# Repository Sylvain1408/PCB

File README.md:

# PCB
Those PCB are done with Cadence and Eagle.

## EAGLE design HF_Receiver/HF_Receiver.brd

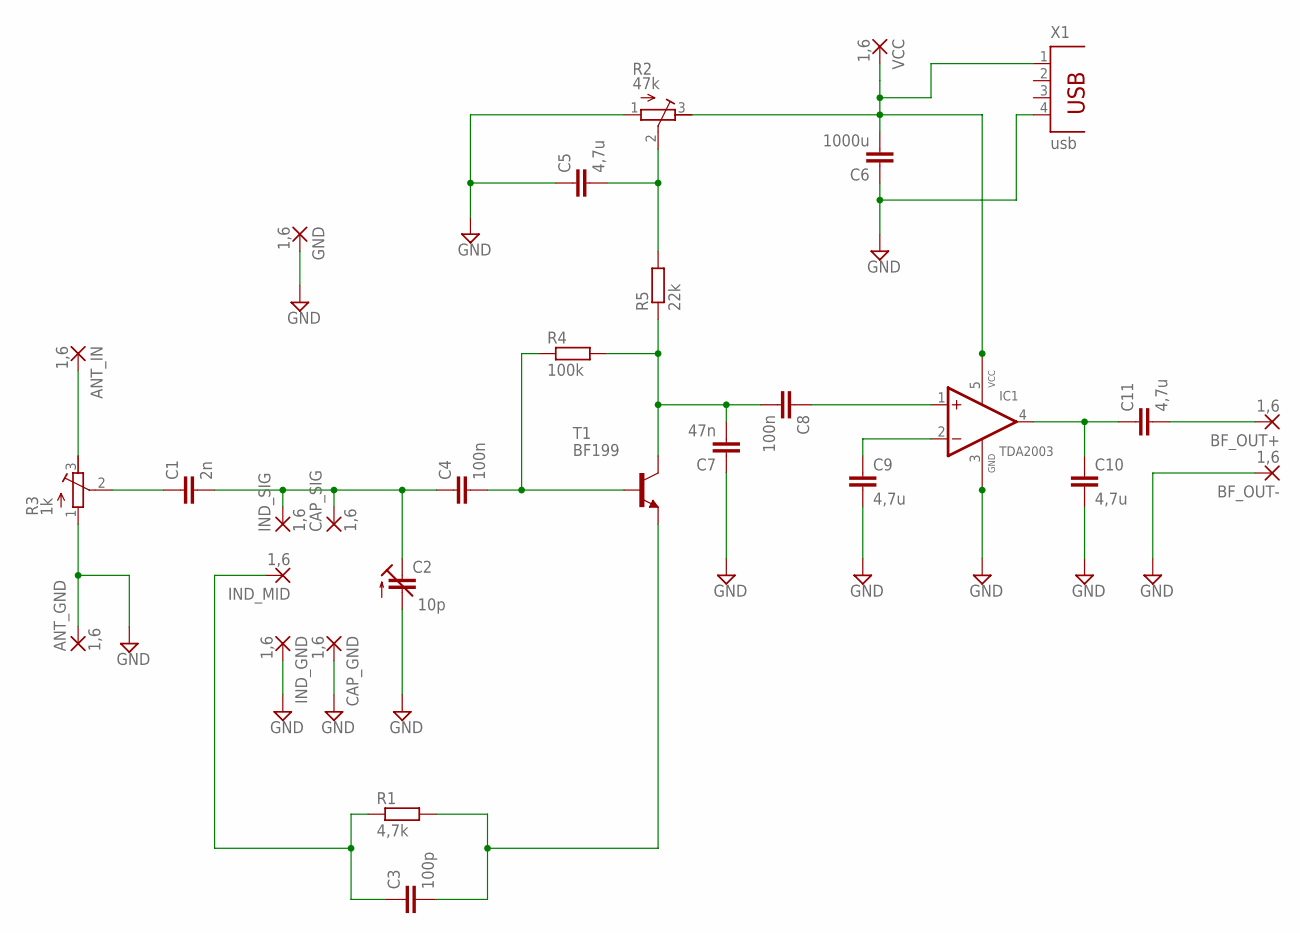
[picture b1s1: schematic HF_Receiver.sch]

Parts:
ANT_GND: 1,6; 1,6/0,9
ANT_IN: 1,6; 1,6/0,9
BF_OUT+: 1,6; 1,6/0,9
BF_OUT-: 1,6; 1,6/0,9
C1: 2n; C075-032X103
C2: 10p; CTRIM808-BC
C3: 100p; C075-032X103
C4, C8: 100n; C075-032X103
C5, C9, C10, C11: 4,7u; C075-032X103
C6: 1000u; C075-032X103
C7: 47n; C075-032X103
CAP_GND: 1,6; 1,6/0,9
CAP_SIG: 1,6; 1,6/0,9
GND: 1,6; 1,6/0,9
IC1: TDA2003; PENTAWATT-V
IND_GND: 1,6; 1,6/0,9
IND_MID: 1,6; 1,6/0,9
IND_SIG: 1,6; 1,6/0,9
R1: 4,7k; 0207/10
R2: 47k; RTRIM3339P
R3: 1k; RTRIM3339P
R4: 100k; 0207/10
R5: 22k; 0207/10
T1: BF199; TO92
VCC: 1,6; 1,6/0,9
X1: usb; PN87520

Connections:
GND: ANT_GND.1, BF_OUT-.1, C2.2 (A), C5.1, C6.1, C7.1, C9.2, C10.2, CAP_GND.1, GND.1, IC1.3 (GND), IND_GND.1, R2.1 (A), R3.1 (A), X1.4
unnamed: ANT_IN.1, R3.3 (E)
unnamed: C1.1, R3.2 (S)
unnamed: C1.2, C2.1 (E), C4.1, CAP_SIG.1, IND_SIG.1
unnamed: C3.1, IND_MID.1, R1.1
unnamed: C3.2, R1.2, T1.2 (E)
unnamed: C4.2, R4.1, T1.1 (B)
unnamed: C8.1, IC1.1 (+IN)
unnamed: C7.2, C8.2, R4.2, R5.1, T1.3 (C)
unnamed: C5.2, R2.2 (S), R5.2
unnamed: C9.1, IC1.2 (-IN)
unnamed: C10.1, C11.1, IC1.4 (OUT)
unnamed: BF_OUT+.1, C11.2
VCC: C6.2, IC1.5 (VCC), R2.3 (E), VCC.1, X1.1

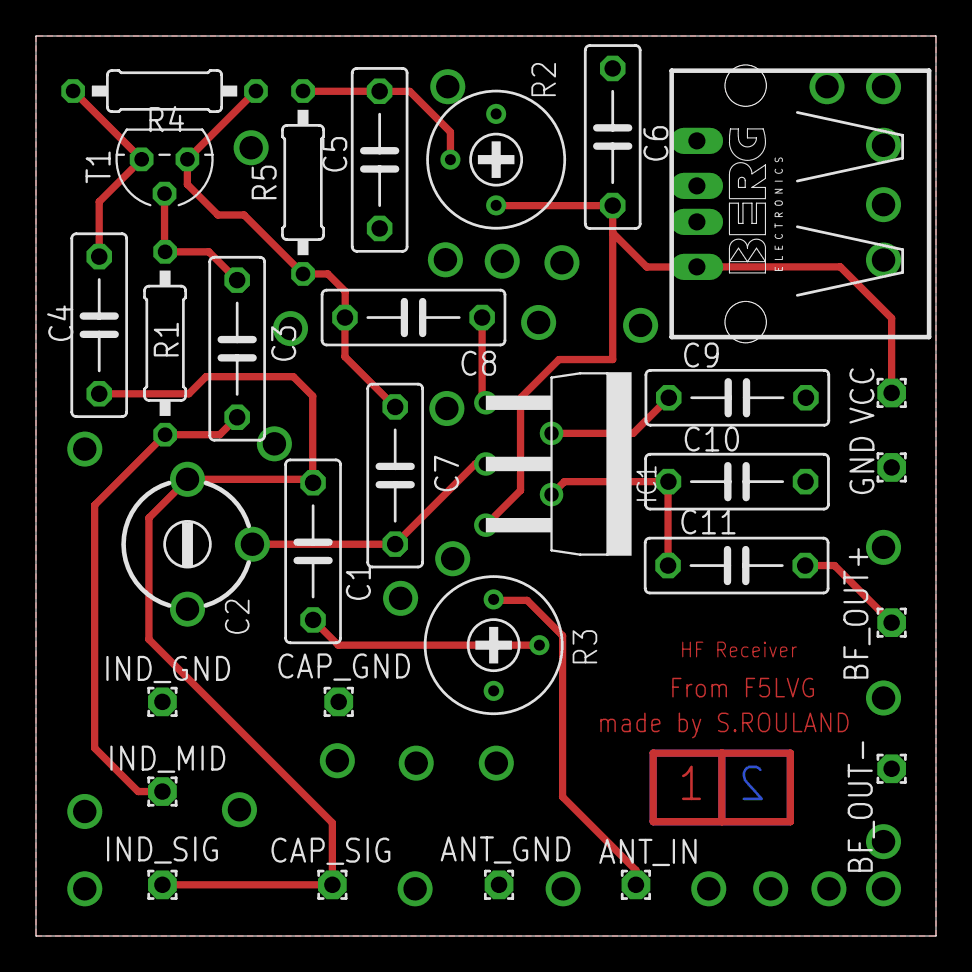
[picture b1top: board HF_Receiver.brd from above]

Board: 2 copper layers, 50.0 x 50.0 mm, 30 parts (0 on the bottom side), 14 nets.

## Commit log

2017-02-04 First commit. Samus PCb badge.
2017-02-18 Add Bottom to Samus.
2017-02-18 Samus Bottom ongoing.
2017-02-20 Almost finish Samus badge. Still remains the back etch.
2017-03-02 Add original photos. Add files to manufacture.
2017-03-18 Add photo of production done by Seedstudio.
2017-03-18 Moving image to proper board file.
2017-04-04 First commit : Evaluation board to test double USB charge switched.
2017-04-05 Add overview and page 2 (second USB and charger).
2017-04-17 Adding HF receiver
2017-05-28 Create component for Rockchip CPU : RK3399
2017-06-15 Split schematic of RK3399 + add datasheet.
2017-06-21 RK3399 U1A done.
2017-06-22 Complete RK3399 U1B
2017-06-22 RK3399 DDR/USB/SDI0/EMMC block done.
2017-06-23 Add RK3399 GPIO2/MIPI/HDMI/PCIE/ADC module.
2017-06-25 RK3399 schematic done, RK808 done, DDR3 Samsung done. Create library for SMD res/capa/ind.
2017-06-26 Add IC_lib (RK3399/808 DDR3 Samsung)
2017-06-28 Create schematic, start implementing RK808 according to firefly schematic.
2017-06-29 Finish RK808 schematic part (create associated components on IC_Lib.OLB/SMD_CAP_LIB.OLB/SMD_RES_LIB.OLB)
2017-07-02 RK3399 GPIO done. Start implementing DDR3 side.
2017-07-03 Correct footprint issue on SMD_LIB_*. Ctd RK3399 implementation.
2017-07-04 Create 201C Footprint. Ctd RK3399 schematic.
2017-07-06 Add SOT-23 & 0201 SMD footprint.
2017-07-06 Create MOSFET N component, 0R,499R,133R,47K resistor.
2017-07-06 Implement RK3399 side : PCIE, ADC, USB, USIC, SDIO, EMMC, DDR.
2017-07-07 RK3399 CAMERA/DISPLAY/GPIO DONE. Add document around RK3399.
2017-07-10 Finish DDR3 implementation. Start general power part.
2017-07-12 Create MOSFET Channel P, BJT NPN, add over temperature protection.
2017-07-13 Complete regulators page. Start eMMc implementation. Add silergy datasheet.
2017-07-15 Create SMARC connector mechanic (both 82x50 & 82x80) + add hardware spec.
2017-07-29 Start routing RK808. Add missing pad/footprint.
2017-08-01 Add DDR rules + Wurth design rules. Test some setup on fanout/DRAM routing.
2017-08-01 Add uvias,
2017-08-02 Placement/routing RK808 part. Place DDR & CPU a final offset.
2017-08-03 Finish setup of constraint for DDR. Start fanout U4/U5. Create TPH with minimal size according to Wurth standard.
2017-08-06 Route Addr part of DDR.
2017-08-06 Correct some 50 ohm impedance for ddr1 data.
2017-08-06 Add via class 7 : 0.2/0.4 + pad for wifi module.
2017-08-22 Routing between CPU/DRAM done. VCC_DDR Capa placed. Ctd PMIC side. Add Wifi footprint
2017-09-04 Create Datasheet & Design_Guide directories.
2017-09-04 Move SYR828-Silergy.pdf & RK3399 hardware reference to Datasheet directory.
2017-09-20 Add Smarc 2.0 pinout excel
2017-09-22 Add connector library with SMARC 2.0 implementation ongoing.
2017-09-22 Wifi implementation ongoing.
2017-09-23 Match length : DDR1 data group 0/2 & DDR1 ADDR
2017-09-27 Smarc 2.0 connector 95% done (page 1 global management to be done).
2017-09-28 SMARC 2.0 fully created.
2017-09-28 Add crystal application note from ST.
2017-09-29 Add DDR3 datasheet.
2017-09-29 Changing DDR routing approach.
2017-10-01 DRAM routing finish : add z axis delay.
2017-10-03 Add HDMI schematic/layout.
2017-10-03 Add 4.7uH coil.
2017-10-03 Wifi/BT schematic ongoing.
2017-10-03 Reduce DRAM left side width.
2017-10-03 Remove .opj useless file.
2017-11-11 Add design guide
    Design guide for BGA, oscillator, pin in paste
    Main project is hidden for now
2019-10-16 Creating project to test components with NanoVNA
2019-10-19 Ctd design
2019-10-23 Add design guide for various things
2019-10-26 Add SMA to SMA
2019-10-26 Quartz capacitive load design note
2019-10-27 Layout done.
    tbd gerber
2019-10-27 Generate manufacturing files
2019-11-02 Creating a switch board to add battery to electric scooter
2019-11-03 start routing
2019-11-16 Capacitor information
2019-11-16 Capacitor for power supply
2019-11-25 Finish board, production ongoing
2019-11-25 Update breaktab according to production review
    holes were plated, almost impossible to break.
2019-12-05 Add NFC antenna design files
2019-12-13 Add CEM doc
2020-01-26 Designing quad-band GSM antenna
2020-02-05 Create a base project with variable parameters for antenna design (+-x, +-y, trace/clearance...)
2020-02-27 Add antenna examples to study
2020-06-08 Add a lot of doc
2020-06-16 Add low level measure handbook
2020-10-29 Commit EMI probe
    Produced, works well
2020-11-26 Add DAC_Filter section
    Add Texas document concerning decimation/interpolation filter
2020-11-27 Adding High Speed, Digital to Analog Converters Basics
2020-12-10 Add webinar from Analog Device
2020-12-22 Some Lecroy oscilloscope stuff
2021-05-11 Add Thermal design guide/calc sheet
2021-11-17 Add Shield/Shield_absorption.xlsx + update
2022-04-14 Add Flyback design guides
2022-04-14 Add additionnal design guides
2022-04-15 Add TVS selection document
2022-04-19 Update RFID circular antenna calculation
2022-05-25 Add simsmith software
2022-06-01 Add ST Antenna design equation
2022-08-09 Move + add BGA application notes
2025-01-07 Add some antenna calculations
2025-01-09 Add IFA array source doc
2025-08-07 Add mm to ps calculation
